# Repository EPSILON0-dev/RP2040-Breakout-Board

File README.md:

# RP2040 Breakout Board

Minimal RP2040 breakout with USB Micro-B, 16 MB QSPI flash, and full GPIO headers in a breadboard-friendly form factor.

---

## Pin Reference

---

## Specifications

| Parameter | Value |
|-----------|-------|
| MCU | RP2040 (dual-core Arm Cortex-M0+ @ up to 133 MHz) |
| Flash | 16 MB W25Q128JVS (QSPI) or compatible |
| Supply voltage | 5 V via USB Micro-B; 3.3 V via onboard AP1117-33 LDO |
| Internal 1.1 V rail | Generated by RP2040 internal LDO (VREG) |
| Clock | 12 MHz external crystal |
| USB | USB Micro-B (power + data) |
| GPIO headers | 2 × 12-pin 2.54 mm (J2, J3) |
| Status | Tested - fully functional |

---

## Schematic and PCB

| Schematic                        | Board                    |
|:--------------------------------:|:------------------------:|
|  |  |

---

## Boot & Reset

| Control | Component | Behaviour |
|---------|-----------|-----------|
| **BOOT** | SW1 (USB_BOOT) | Hold while connecting USB to enter USB bootloader (UF2 mode). Pulls QSPI_SS low via R1 (1 kΩ); R2 (47 kΩ) pulls QSPI_SS high normally. |
| **RESET** | SW2 (RESET) | Momentarily pulls RUN low. R3 (10 kΩ) holds RUN high during normal operation. |

---

## Manufacturing

Gerber files are in the [`gerber/`](gerber/) directory, ready to upload to JLCPCB, PCBWay, or equivalent.

Suggested fab settings:

| Setting | Value |
|---------|-------|
| Layers | 4 (F_Cu, In1_Cu, In2_Cu, B_Cu) |
| Thickness | 1.6 mm |
| Surface finish | HASL (lead-free) or ENIG |

---

## Status

- [x] Designed, not yet ordered
- [x] Ordered — awaiting boards
- [x] Assembled, untested
- [x] Tested and working

---

## Building / Programming

### USB Bootloader (UF2)

```bash
# 1. Hold SW1 (BOOT button) and connect USB — board appears as RPI-RP2 mass storage
# 2. Drag and drop a UF2 firmware image
cp firmware.uf2 /media/$USER/RPI-RP2
```

---

## License

Licensed under the MIT [License](LICENSE)

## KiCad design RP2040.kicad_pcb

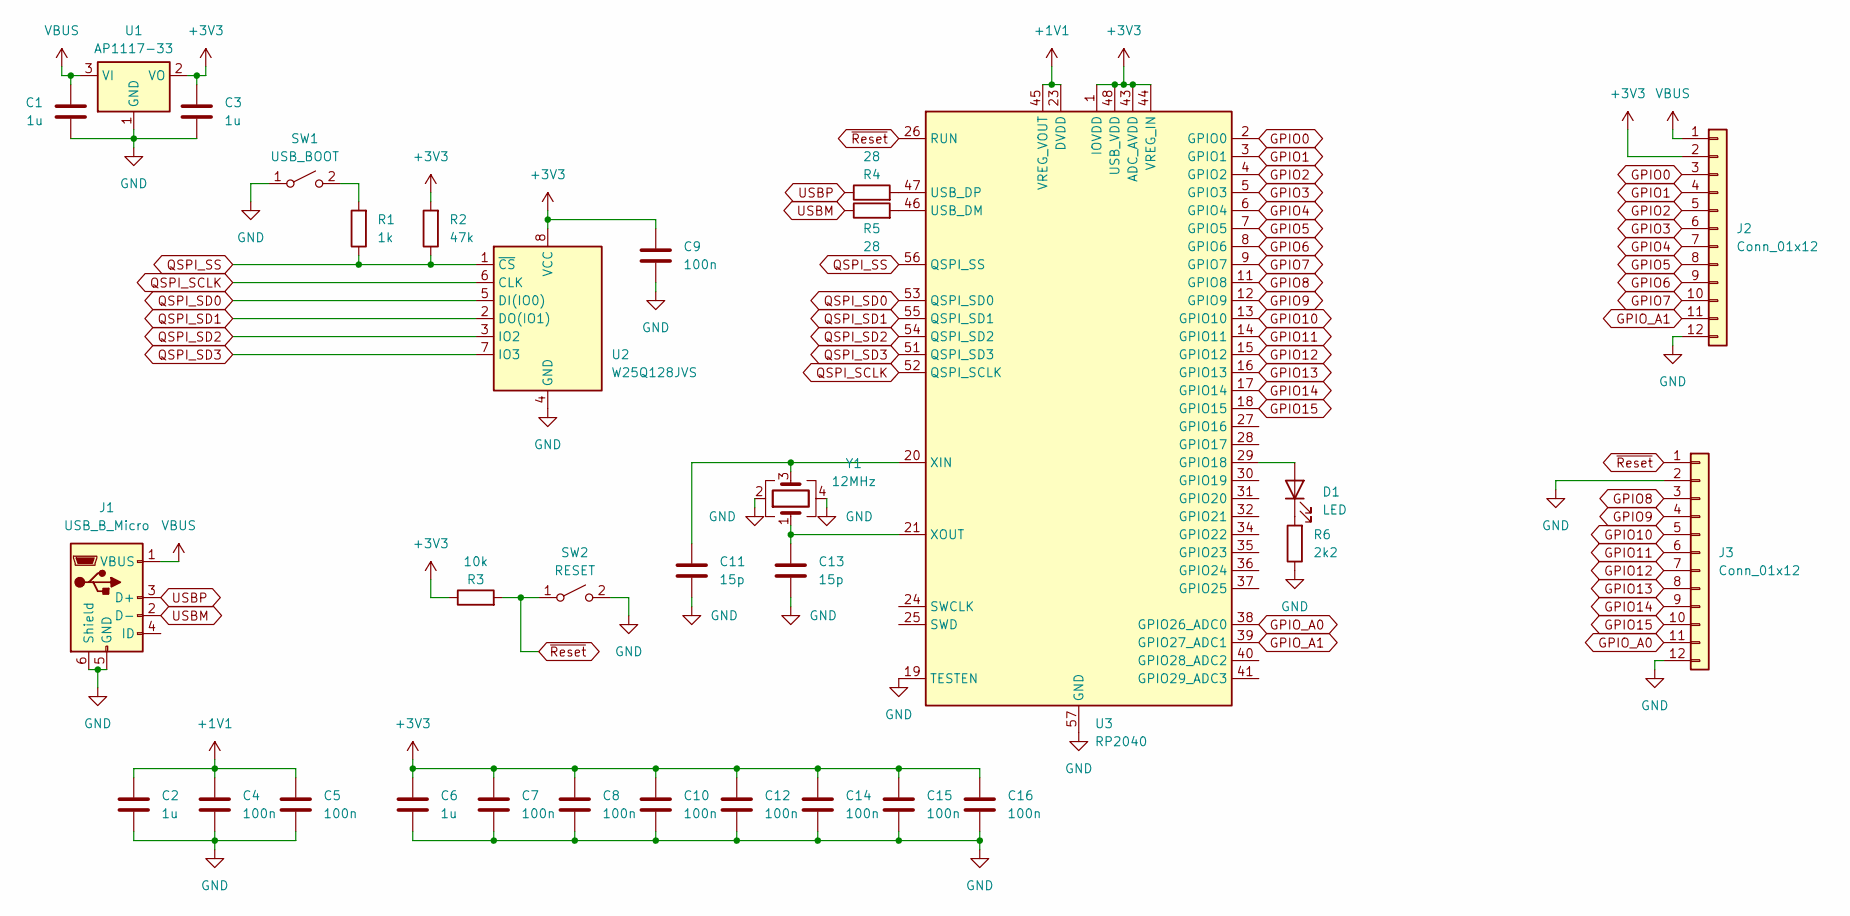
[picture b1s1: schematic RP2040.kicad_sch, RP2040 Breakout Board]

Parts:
C1, C2, C3, C6: 1u; C_0603_1608Metric
C4, C5, C7, C8, C9, C10, C12, C14, C15, C16: 100n; C_0603_1608Metric
C11, C13: 15p; C_0603_1608Metric
D1: LED; LED_0805_2012Metric
J1: USB_B_Micro; USB_Micro-B_Molex_47346-0001
J2, J3: Conn_01x12; PinHeader_1x12_P2.54mm_Vertical
R1: 1k; R_0603_1608Metric
R2: 47k; R_0603_1608Metric
R3: 10k; R_0603_1608Metric
R4, R5: 28; R_0603_1608Metric
R6: 2k2; R_0603_1608Metric
SW1: USB_BOOT; SW_SPST_EVQP2
SW2: RESET; SW_SPST_EVQP2
U1: AP1117-33; SOT-223-3_TabPin2
U2: W25Q128JVS; WSON-8-1EP_6x5mm_P1.27mm_EP3.4x4mm
U3: RP2040; QFN-56-1EP_7x7mm_P0.4mm_EP3.2x3.2mm
Y1: 12MHz; Crystal_SMD_3225-4Pin_3.2x2.5mm

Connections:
+1V1: C2.1, C4.1, C5.1, U3.23 (DVDD), U3.45 (VREG_VOUT), U3.50 (DVDD)
+3V3: C3.1, C6.1, C7.1, C8.1, C9.1, C10.1, C12.1, C14.1, C15.1, C16.1, J2.2, R2.2, R3.1, U1.2 (VO), U2.8 (VCC), U3.1 (IOVDD), U3.10 (IOVDD), U3.22 (IOVDD), U3.33 (IOVDD), U3.42 (IOVDD), U3.43 (ADC_AVDD), U3.44 (VREG_IN), U3.48 (USB_VDD), U3.49 (IOVDD)
GND: C1.2, C2.2, C3.2, C4.2, C5.2, C6.2, C7.2, C8.2, C9.2, C10.2, C11.2, C12.2, C13.2, C14.2, C15.2, C16.2, J1.5 (GND), J1.6 (Shield), J2.12, J3.2, J3.12, R6.1, SW1.1 (A), SW2.2 (B), U1.1 (GND), U2.4 (GND), U3.19 (TESTEN), U3.57 (GND), Y1.2, Y1.4
GPIO0: J2.3, U3.2 (GPIO0)
GPIO1: J2.4, U3.3 (GPIO1)
GPIO2: J2.5, U3.4 (GPIO2)
GPIO3: J2.6, U3.5 (GPIO3)
GPIO4: J2.7, U3.6 (GPIO4)
GPIO5: J2.8, U3.7 (GPIO5)
GPIO6: J2.9, U3.8 (GPIO6)
GPIO7: J2.10, U3.9 (GPIO7)
GPIO8: J3.3, U3.11 (GPIO8)
GPIO9: J3.4, U3.12 (GPIO9)
GPIO10: J3.5, U3.13 (GPIO10)
GPIO11: J3.6, U3.14 (GPIO11)
GPIO12: J3.7, U3.15 (GPIO12)
GPIO13: J3.8, U3.16 (GPIO13)
GPIO14: J3.9, U3.17 (GPIO14)
GPIO15: J3.10, U3.18 (GPIO15)
GPIO_A0: J3.11, U3.38 (GPIO26_ADC0)
GPIO_A1: J2.11, U3.39 (GPIO27_ADC1)
unnamed: D1.2 (A), U3.29 (GPIO18)
unnamed: D1.1 (K), R6.2
unnamed: R1.2, SW1.2 (B)
unnamed: R5.2, U3.46 (USB_DM)
unnamed: R4.2, U3.47 (USB_DP)
unnamed: C11.1, U3.20 (XIN), Y1.3
unnamed: C13.1, U3.21 (XOUT), Y1.1
QSPI_SCLK: U2.6 (CLK), U3.52 (QSPI_SCLK)
QSPI_SD0: U2.5 (DI(IO0)), U3.53 (QSPI_SD0)
QSPI_SD1: U2.2 (DO(IO1)), U3.55 (QSPI_SD1)
QSPI_SD2: U2.3 (IO2), U3.54 (QSPI_SD2)
QSPI_SD3: U2.7 (IO3), U3.51 (QSPI_SD3)
QSPI_SS: R1.1, R2.1, U2.1 (~CS), U3.56 (QSPI_SS)
USBM: J1.2 (D-), R5.1
USBP: J1.3 (D+), R4.1
VBUS: C1.1, J1.1 (VBUS), J2.1, U1.3 (VI)
~Reset: J3.1, R3.2, SW2.1 (A), U3.26 (RUN)

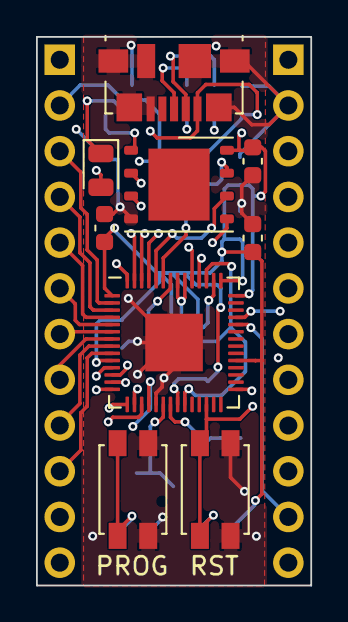
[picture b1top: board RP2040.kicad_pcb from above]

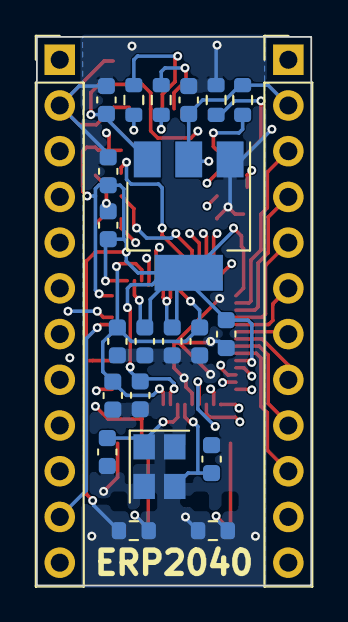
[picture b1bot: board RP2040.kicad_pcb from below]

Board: 4 copper layers, 15.2 x 30.5 mm, 32 parts (23 on the bottom side), 38 nets.

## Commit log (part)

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2026-04-27 fix: remove redundant file(s)
2026-04-27 docs: fix docs
2026-04-27 fix: Fix crystal orientation
2026-04-27 fix: fix schematic and redundant files
2026-04-27 feat: Improve render
2026-04-30 fix: resize images so they load faster
